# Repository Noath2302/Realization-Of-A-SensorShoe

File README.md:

# Realization-Of-A-SensorShoe
Thesis Project SoSe 2019
using sensor to build a plantar data measuring system.
Sensor : accelerator, angle velocity, ground repulsion force when walking.
Data was sent from Esp8266 to a hosting LAN server (socket running on a laptop, harder case for smartphones)

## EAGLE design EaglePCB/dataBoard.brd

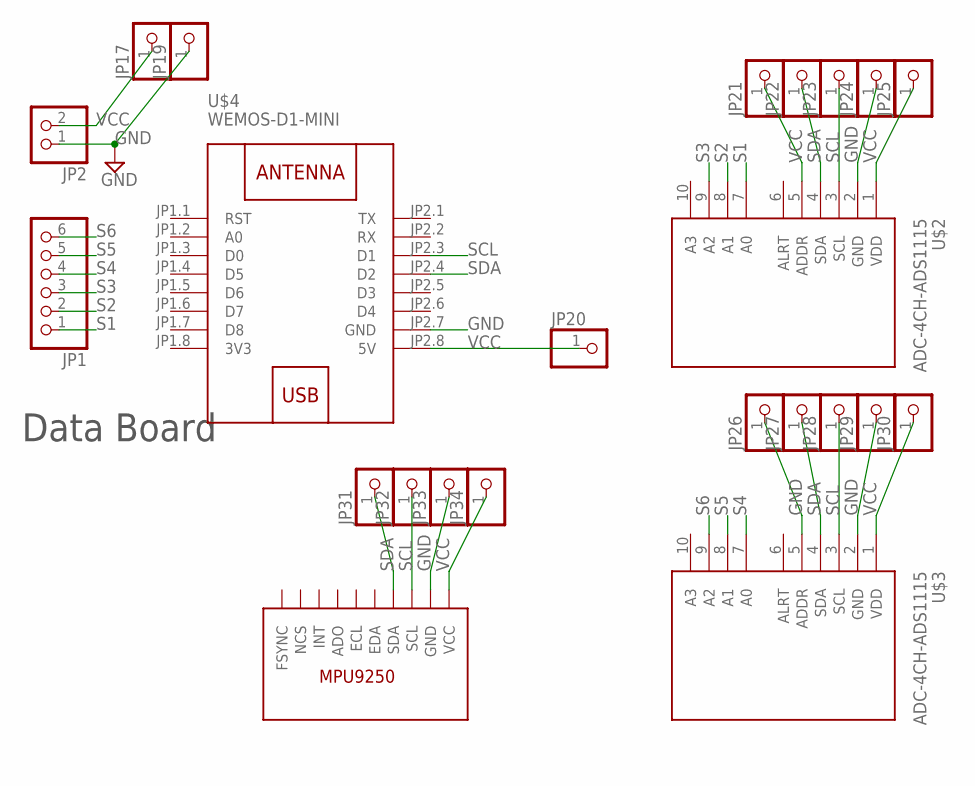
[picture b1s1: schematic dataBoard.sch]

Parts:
JP1: PINHD-1X6; 1X06
JP2: PINHD-1X2; 1X02
JP17, JP19, JP20, JP21, JP22, JP23, JP24, JP25, JP26, JP27, JP28, JP29, JP30, JP31, JP32, JP33, JP34: PINHD-1X1; 1X01
MPU1: MPU9250
U$2, U$3: ADC-4CH-ADS1115
U$4: WEMOS-D1-MINI

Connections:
3V3: U$4.JP1.8 (3V3)
GND: JP2.1, JP19.1, JP24.1, JP26.1, JP29.1, JP33.1, MPU1.GND, U$2.2 (GND), U$3.2 (GND), U$3.5 (ADDR), U$4.JP2.7 (GND)
S1: JP1.1, U$2.7 (A0)
S2: JP1.2, U$2.8 (A1)
S3: JP1.3, U$2.9 (A2)
S4: JP1.4, U$3.7 (A0)
S5: JP1.5, U$3.8 (A1)
S6: JP1.6, U$3.9 (A2)
SCL: JP23.1, JP28.1, JP32.1, MPU1.SCL, U$2.3 (SCL), U$3.3 (SCL), U$4.JP2.3 (D1)
SDA: JP22.1, JP27.1, JP31.1, MPU1.SDA, U$2.4 (SDA), U$3.4 (SDA), U$4.JP2.4 (D2)
VCC: JP2.2, JP17.1, JP20.1, JP21.1, JP25.1, JP30.1, JP34.1, MPU1.VCC, U$2.1 (VDD), U$2.5 (ADDR), U$3.1 (VDD), U$4.JP2.8 (5V)

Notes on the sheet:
Data Board

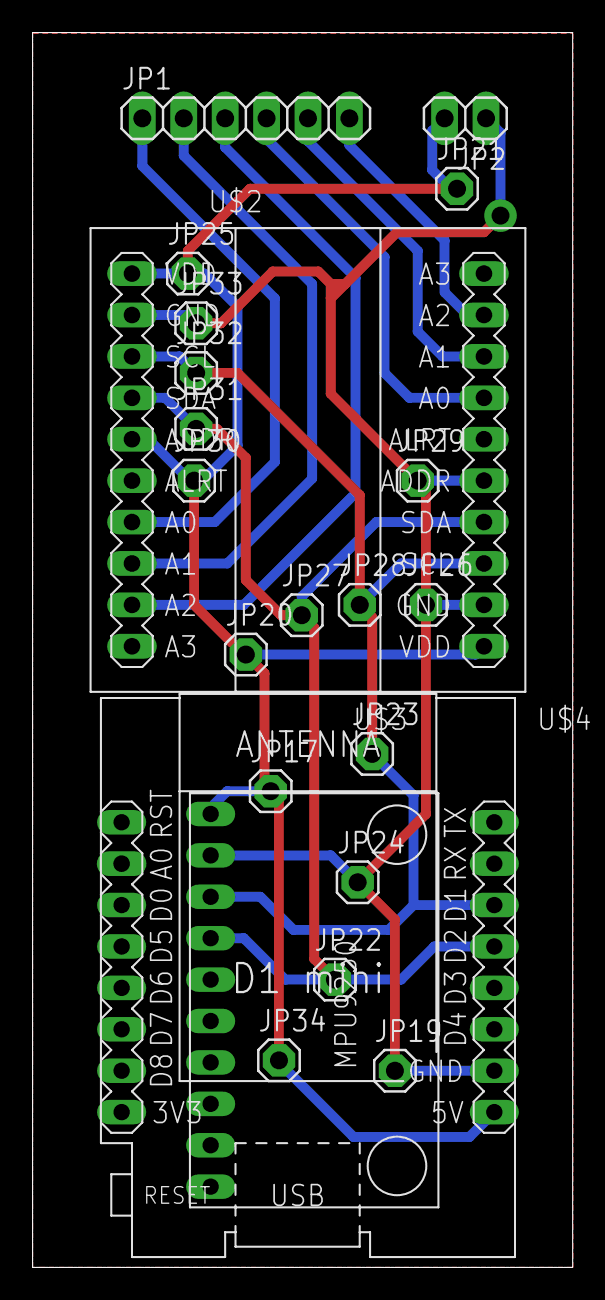
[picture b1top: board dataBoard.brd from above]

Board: 2 copper layers, 33.1 x 75.7 mm, 23 parts (0 on the bottom side), 10 nets.

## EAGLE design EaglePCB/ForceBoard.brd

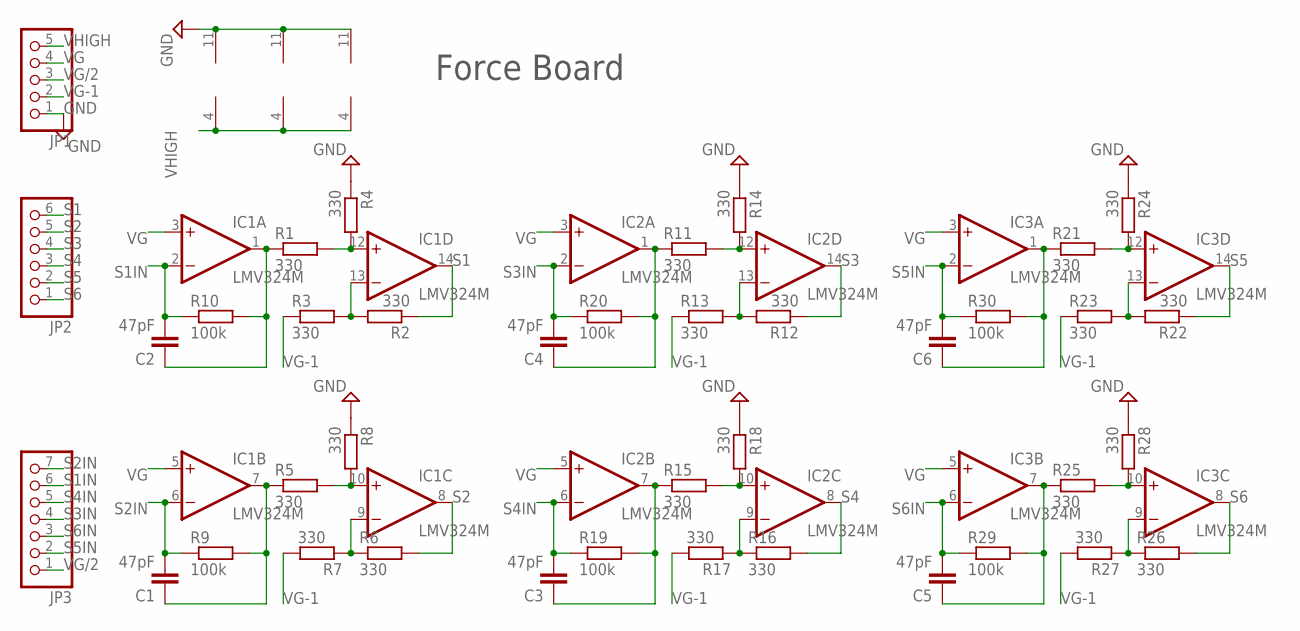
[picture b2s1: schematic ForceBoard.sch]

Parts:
C1, C2, C3, C4, C5, C6: 47pF; C0805
IC1, IC2, IC3: LMV324M; SO14
JP1: PINHD-1X5; 1X05
JP2: PINHD-1X6; 1X06
JP3: PINHD-1X7; 1X07
R1, R2, R3, R4, R5, R6, R7, R8, R11, R12, R13, R14, R15, R16, R17, R18, R21, R22, R23, R24, R25, R26, R27, R28: 330; R0805
R9, R10, R19, R20, R29, R30: 100k; R0805

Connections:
GND: IC1.11 (V-), IC2.11 (V-), IC3.11 (V-), JP1.1, R4.1, R8.1, R14.1, R18.1, R24.1, R28.1
unnamed: IC2.13 (-IN), R12.2, R13.2
unnamed: IC1.10 (+IN), R5.2, R8.2
unnamed: IC1.13 (-IN), R2.2, R3.2
unnamed: C1.1, IC1.7 (OUT), R5.1, R9.2
unnamed: IC1.9 (-IN), R6.1, R7.1
unnamed: IC1.12 (+IN), R1.2, R4.2
unnamed: C3.1, IC2.7 (OUT), R15.1, R19.2
unnamed: IC2.9 (-IN), R16.1, R17.1
unnamed: C2.1, IC1.1 (OUT), R1.1, R10.2
unnamed: IC2.10 (+IN), R15.2, R18.2
unnamed: IC2.12 (+IN), R11.2, R14.2
unnamed: C4.1, IC2.1 (OUT), R11.1, R20.2
unnamed: IC3.13 (-IN), R22.2, R23.2
unnamed: C5.1, IC3.7 (OUT), R25.1, R29.2
unnamed: IC3.9 (-IN), R26.1, R27.1
unnamed: IC3.10 (+IN), R25.2, R28.2
unnamed: IC3.12 (+IN), R21.2, R24.2
unnamed: C6.1, IC3.1 (OUT), R21.1, R30.2
S1: IC1.14 (OUT), JP2.6, R2.1
S1IN: C2.2, IC1.2 (-IN), JP3.6, R10.1
S2: IC1.8 (OUT), JP2.5, R6.2
S2IN: C1.2, IC1.6 (-IN), JP3.7, R9.1
S3: IC2.14 (OUT), JP2.4, R12.1
S3IN: C4.2, IC2.2 (-IN), JP3.4, R20.1
S4: IC2.8 (OUT), JP2.3, R16.2
S4IN: C3.2, IC2.6 (-IN), JP3.5, R19.1
S5: IC3.14 (OUT), JP2.2, R22.1
S5IN: C6.2, IC3.2 (-IN), JP3.2, R30.1
S6: IC3.8 (OUT), JP2.1, R26.2
S6IN: C5.2, IC3.6 (-IN), JP3.3, R29.1
VG: IC1.3 (+IN), IC1.5 (+IN), IC2.3 (+IN), IC2.5 (+IN), IC3.3 (+IN), IC3.5 (+IN), JP1.4
VG-1: JP1.2, R3.1, R7.2, R13.1, R17.2, R23.1, R27.2
VG/2: JP1.3, JP3.1
VHIGH: IC1.4 (V+), IC2.4 (V+), IC3.4 (V+), JP1.5

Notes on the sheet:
Force Board

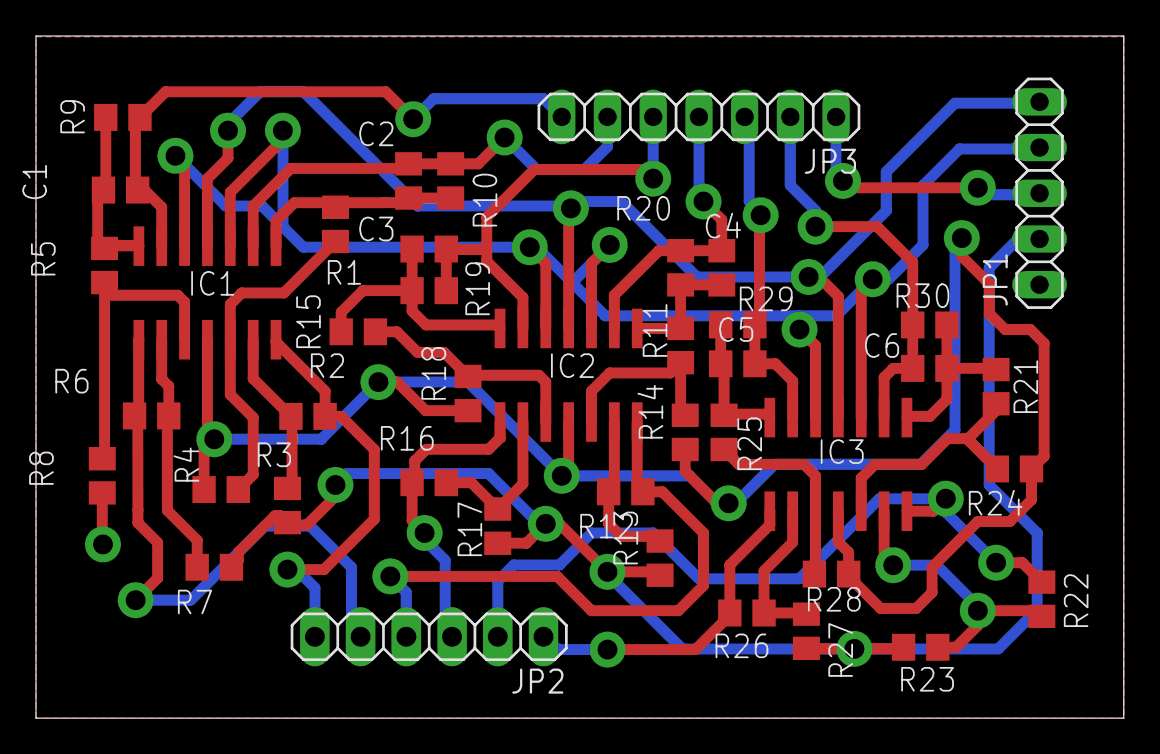
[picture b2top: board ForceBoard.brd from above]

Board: 2 copper layers, 60.4 x 37.9 mm, 42 parts (0 on the bottom side), 35 nets.

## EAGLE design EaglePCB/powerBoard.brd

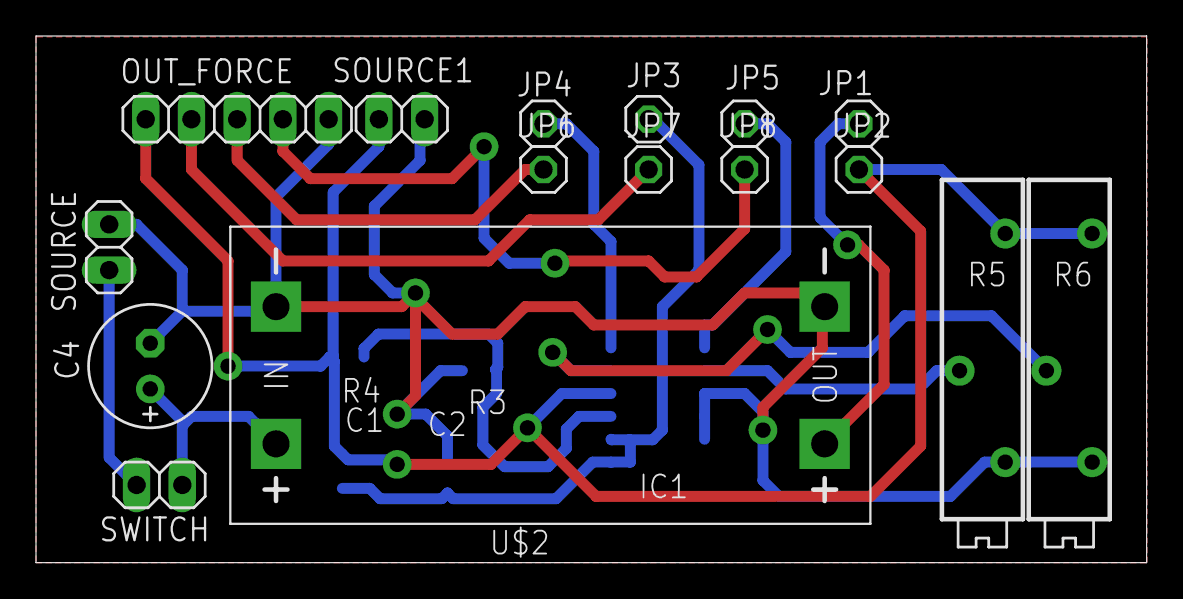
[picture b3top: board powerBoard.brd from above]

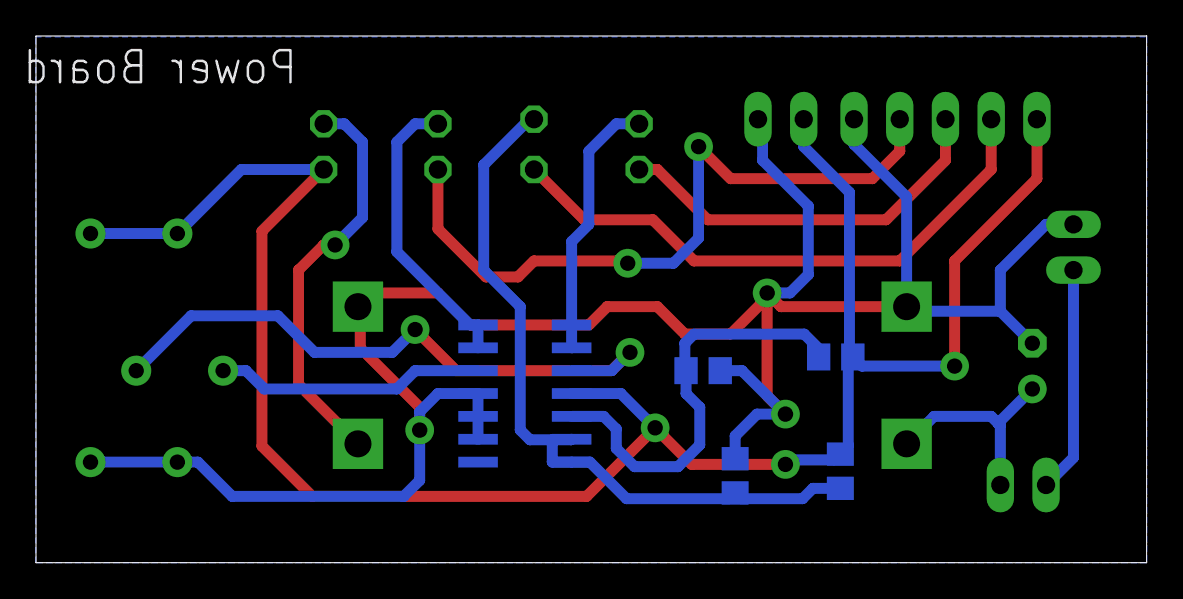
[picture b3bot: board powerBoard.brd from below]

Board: 2 copper layers, 61.7 x 29.3 mm, 21 parts (5 on the bottom side), 14 nets.

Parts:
C1, C2: 47uF; C0805
C4: E2,5-7
IC1: LMV324M; SO14
JP1, JP2, JP3, JP4, JP5, JP6, JP7, JP8: 1X01
OUT_FORCE: 1X05
R3, R4: 10k; R0805
R5, R6: 100k; RTRIM3006P
SOURCE, SOURCE1: 1X02
SWITCH: 1X02
U$2: DC-DC-STEP-UP-MT3608

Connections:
GND: C2.2, C4.-, IC1.11, IC1.12, IC1.13, OUT_FORCE.5, R3.1, R5.3, R6.3, SOURCE.1, SOURCE1.2, U$2.IN-, U$2.OUT-
unnamed: JP1.1, U$2.OUT+
unnamed: IC1.3, R3.2, R4.2
unnamed: SOURCE.2, SWITCH.1
unnamed: C4.+, SWITCH.2, U$2.IN+
unnamed: IC1.10, R5.2
unnamed: IC1.5, R6.2
unnamed: JP8.1, OUT_FORCE.4
unnamed: JP6.1, OUT_FORCE.3
unnamed: JP7.1, OUT_FORCE.2
VG: C1.2, C2.1, IC1.1, IC1.2, JP3.1
VG-1: IC1.8, IC1.9, JP5.1
VG/2: IC1.6, IC1.7, JP4.1
VHIGH: C1.1, IC1.4, JP2.1, OUT_FORCE.1, R4.1, R5.1, R6.1, SOURCE1.1

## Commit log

2019-10-09 adding .gitignore
2019-10-09 remove pptx file from the repository
2019-10-09 remove unnescessary files
2019-10-09 modified .gitignore to keep oldFiles in Folder
2019-11-06 adding MIT license
    making my work accessible
2020-08-15 adding Eagle PCBs

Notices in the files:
parts and their libraries:
diy-modules_me: Released under the Creative Commons Attribution 4.0 International License: http://creativecommons.org/licenses/by/4.0
